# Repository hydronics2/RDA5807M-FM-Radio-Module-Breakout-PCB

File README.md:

# RDA5807M-FM-Radio-Module-Breakout-PCB

This is a simple breakout board for a RDA5807 Radio Module available for less than $1. This PCB was designed in Eagle. The PCB can be purchased through [oshpark](https://oshpark.com/shared_projects/gvh1B0PT). For prototyping connectors I used screw terminals at 5.08mm pitch [like these](https://www.aliexpress.com/wholesale?catId=0&initiative_id=SB_20190221213812&SearchText=screw+terminal+block+5.08mm).

The RDA 5807M is single chip broadcast FM stereo Radio tuner with both frequency selection and RDS/RBDS decoder over i2c. The RDA5807M series support FM bands 50MHz to 115MHz. [link to cutsheet](http://cxem.net/tuner/files/tuner84_RDA5807M_datasheet_v1.pdf)

I'll be using the arduion IDE to program a microcontroller to use the RDA5807M.

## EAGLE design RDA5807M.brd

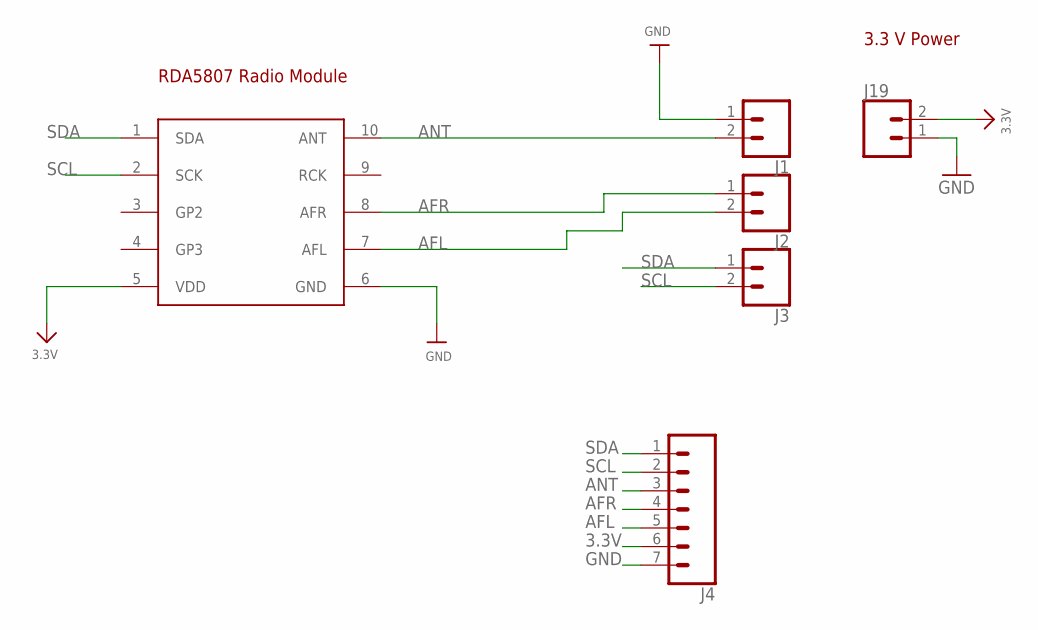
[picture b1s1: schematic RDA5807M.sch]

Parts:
J1, J2, J3, J19: CONN_025MM; SCREWTERMINAL-5MM-2
J4: CONN_07; 1X07
U$17: RDA5807_RADIO; RDA5807

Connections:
3.3V: J4.6, J19.2, U$17.5 (VDD)
AFL: J2.2, J4.5, U$17.7 (AFL)
AFR: J2.1, J4.4, U$17.8 (AFR)
ANT: J1.2, J4.3, U$17.10 (ANT)
GND: J1.1, J4.7, J19.1, U$17.6 (GND)
SCL: J3.2, J4.2, U$17.2 (SCK)
SDA: J3.1, J4.1, U$17.1 (SDA)

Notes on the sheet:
RDA5807 Radio Module
3.3 V Power

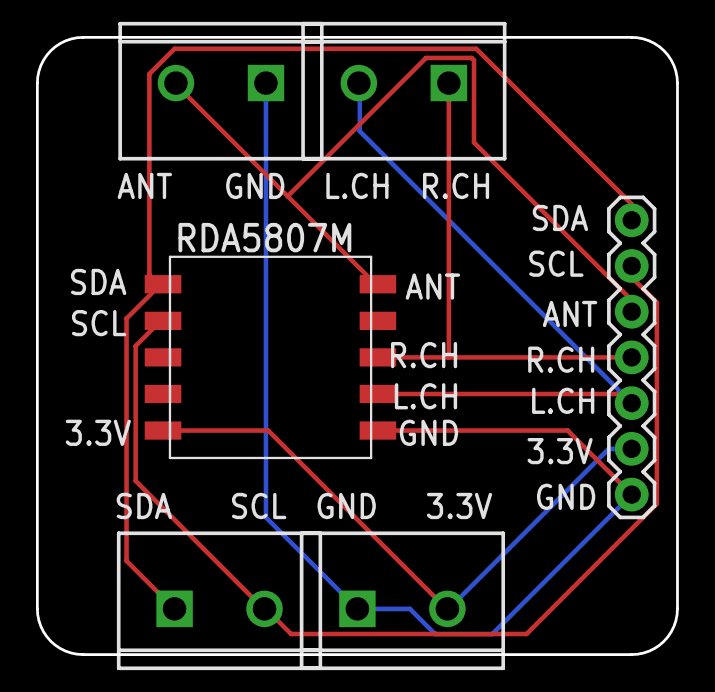
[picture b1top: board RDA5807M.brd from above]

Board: 2 copper layers, 35.6 x 34.3 mm, 6 parts (0 on the bottom side), 7 nets.

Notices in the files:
parts and their libraries:
SparkFun-Connectors: Licensing: Creative Commons ShareAlike 4.0 International - https://creativecommons.org/licenses/by-sa/4.0
microbuilder: This work is placed in the public domain, and may be freely used for commercial and non-commercial work with the following conditions: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
